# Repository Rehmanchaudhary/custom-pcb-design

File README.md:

# Custom PCB Design — Arduino Nano Clone

Full schematic and PCB layout design of an Arduino Nano–compatible board, designed
from scratch in KiCad, physically etched, soldered, and tested.

## What's Included
- `Arduino_Nano.kicad_sch` — full schematic
- `Arduino_Nano.kicad_pcb` — routed PCB layout (39 components placed)

## Key Components
- **ATmega328P** — main microcontroller
- **FT232RL** — USB-to-serial converter for programming/communication
- **LM1117MP-5.0** — 5V linear voltage regulator
- **USB Mini-B connector** — power and data
- **16MHz crystal resonator** — clock source
- Supporting passives: resistors, capacitors, status LEDs, polyfuse, reset switch

## How It Works
The design replicates the core architecture of an Arduino Nano: USB power and
serial communication are handled by the FT232RL, which bridges to the ATmega328P
over its UART pins for programming. The LM1117 regulates incoming USB 5V down to
a clean supply rail for the logic, with decoupling capacitors placed close to
each IC to maintain signal integrity. The resonator provides the microcontroller's
clock signal.

## Process
1. Schematic capture in KiCad — placing and wiring all components with correct
   pin assignments and power nets
2. PCB layout — routing traces, placing components, checking for clearance/DRC
   errors
3. Physical fabrication — etching the board
4. Assembly — soldering all components onto the etched board
5. Testing — verifying continuity and functionality of the assembled board

## Tech Stack
`KiCad` `PCB Design` `Schematic Capture` `Circuit Etching` `Soldering`

## What I Learned
Routing traces without accidental shorts was the hardest part of the layout stage —
with a board this dense (39 components including a microcontroller, USB-to-serial
chip, and voltage regulator), keeping enough clearance between traces while still
routing everything cleanly took several passes through KiCad's design rule checker.
Etching and soldering the physical board afterward made clear how much a clean
schematic and layout actually matters — any mistake at the design stage becomes a
much harder problem to fix once it's etched into copper.

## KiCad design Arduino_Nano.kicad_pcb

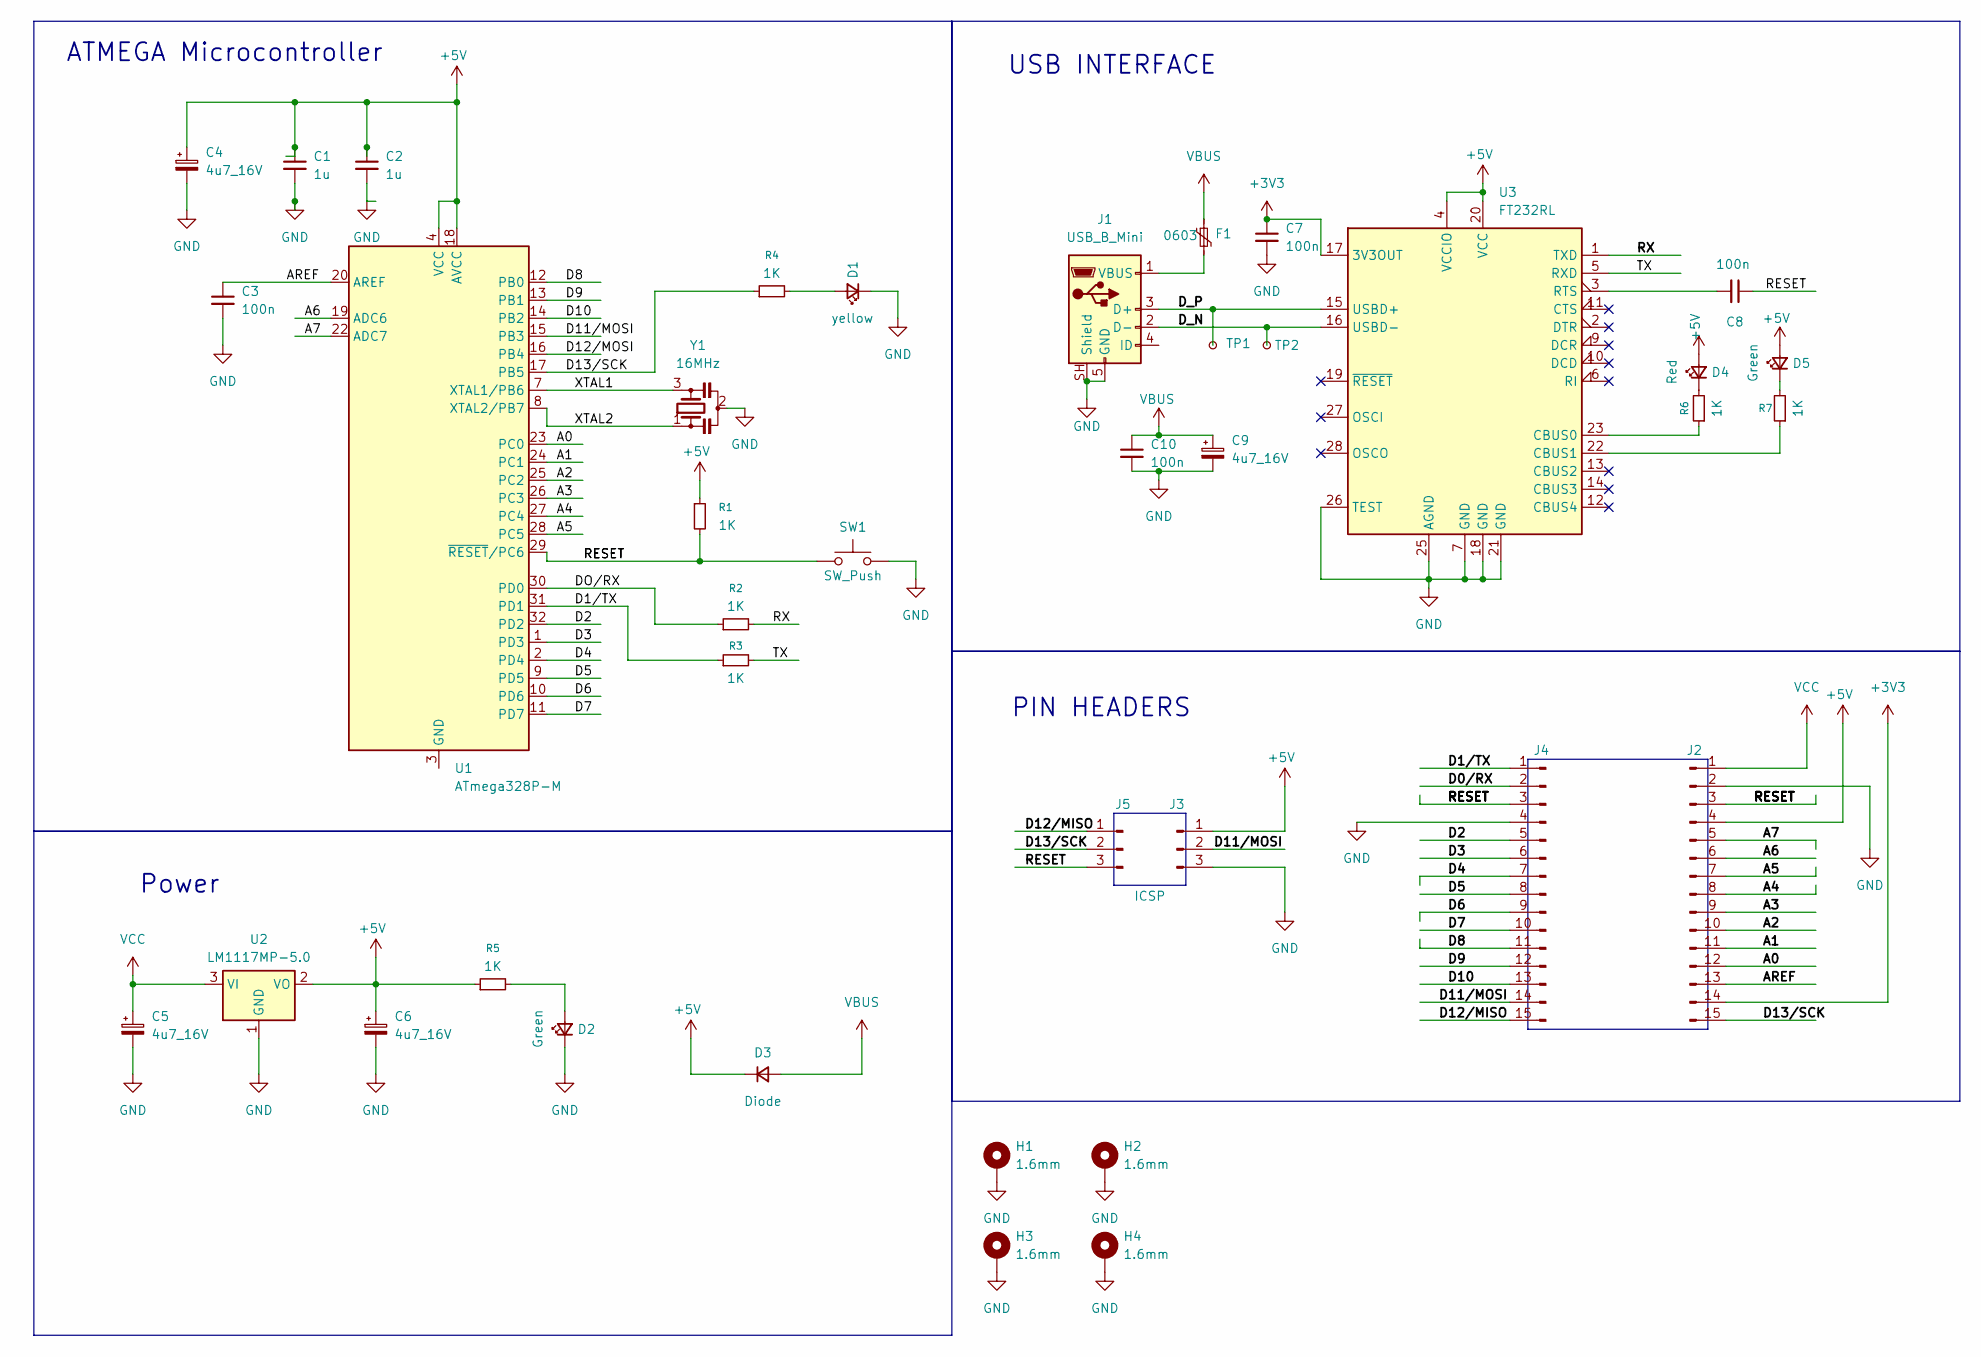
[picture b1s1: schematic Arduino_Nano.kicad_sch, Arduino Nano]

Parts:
C1, C2: 1u; C_0805_2012Metric
C3, C7, C10: 100n; C_0805_2012Metric
C4, C5, C6, C9: 4u7_16V; C_0805_2012Metric
C8: 100n; CP_EIA-3216-18_Kemet-A
D1: yellow; LED_0805_2012Metric
D2, D5: Green; LED_0805_2012Metric
D3: Diode; D_SOD-123
D4: Red; LED_0805_2012Metric
F1: 0603; Fuse_0603_1608Metric
H1, H2, H3, H4: 1.6mm; MountingHole_3.2mm_M3_DIN965_Pad
J1: USB_B_Mini; USB_Mini-B_Lumberg_2486_01_Horizontal
J2, J4: PinHeader_1x15_P2.54mm_Vertical
J3: ICSP; PinHeader_2x03_P2.54mm_Vertical
J5: PinHeader_1x03_P2.54mm_Vertical
R1, R2, R3, R4, R5, R6, R7: 1K; R_0805_2012Metric
SW1: SW_Push; SW_SPST_TL3342
TP1, TP2: TestPoint_Pad_D1.5mm
U1: ATmega328P-M; TQFP-48-1EP_7x7mm_P0.5mm_EP5x5mm
U2: LM1117MP-5.0; SOT-223-3_TabPin2
U3: FT232RL; SSOP-28_5.3x10.2mm_P0.65mm
Y1: 16MHz; Crystal_SMD_SeikoEpson_FA128-4Pin_2.0x1.6mm

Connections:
+3V3: C7.1, J2.14, U3.17 (3V3OUT)
+5V: C1.1, C2.1, C4.1, C6.1, D3.1 (K), D4.2 (A), D5.2 (A), J2.4, J3.1, R1.1, R5.1, U1.4 (VCC), U1.6 (VCC), U1.18 (AVCC), U2.2 (VO), U3.4 (VCCIO), U3.20 (VCC)
/A0: J2.12, U1.23 (PC0)
/A1: J2.11, U1.24 (PC1)
/A2: J2.10, U1.25 (PC2)
/A3: J2.9, U1.26 (PC3)
/A4: J2.8, U1.27 (PC4)
/A5: J2.7, U1.28 (PC5)
/A6: J2.6, U1.19 (ADC6)
/A7: J2.5, U1.22 (ADC7)
/AREF: C3.1, J2.13, U1.20 (AREF)
/D0/RX: J4.2
/D1/TX: J4.1, R3.1, U1.31 (PD1)
/D2: J4.5, U1.32 (PD2)
/D3: J4.6, U1.1 (PD3)
/D4: J4.7, U1.2 (PD4)
/D5: J4.8, U1.9 (PD5)
/D6: J4.9, U1.10 (PD6)
/D7: J4.10, U1.11 (PD7)
/D8: J4.11, U1.12 (PB0)
/D9: J4.12, U1.13 (PB1)
/D10: J4.13, U1.14 (PB2)
/D11/MOSI: J3.2, J4.14, U1.15 (PB3)
/D12/MISO: J4.15, J5.1
/D12/MOSI: U1.16 (PB4)
/D13/SCK: J2.15, J5.2, R4.1, U1.17 (PB5)
/DO/RX: R2.1, U1.30 (PD0)
/D_N: J1.2 (D-), TP2.1 (1_1), U3.16 (USBD-)
/D_P: J1.3 (D+), TP1.1 (1_1), U3.15 (USBD+)
/RX: R2.2, U3.1 (TXD)
/TX: R3.2, U3.5 (RXD)
/XTAL1: U1.7 (XTAL1/PB6), Y1.3
/XTAL2: U1.8 (XTAL2/PB7), Y1.1
GND: C1.2, C2.2, C3.2, C4.2, C5.2, C6.2, C7.2, C9.2, C10.2, D1.1 (K), D2.1 (K), H1.1 (1_1), H2.1 (1_1), H3.1 (1_1), H4.1 (1_1), J1.5 (GND), J1.SH (Shield), J2.2, J3.3, J4.4, SW1.2, U2.1 (GND), U3.7 (GND), U3.18 (GND), U3.21 (GND), U3.25 (AGND), U3.26 (TEST), Y1.2
unnamed: D1.2 (A), R4.2
unnamed: D2.2 (A), R5.2
unnamed: D4.1 (K), R6.2
unnamed: D5.1 (K), R7.2
unnamed: F1.2, J1.1 (VBUS)
unnamed: U1.3 (GND), U1.5 (GND), U1.21 (GND), U1.33 (GND)
unnamed: R6.1, U3.23 (CBUS0)
unnamed: R7.1, U3.22 (CBUS1)
unnamed: C8.2, U3.3 (RTS)
VBUS: C9.1, C10.1, D3.2 (A), F1.1
VCC: C5.1, J2.1, U2.3 (VI)

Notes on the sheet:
Power
PIN HEADERS
ATMEGA Microcontroller
USB INTERFACE

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
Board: 2 copper layers, 39 parts (0 on the bottom side), 45 nets, no tracks yet.
